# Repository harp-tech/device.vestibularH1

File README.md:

## Harp VestibularH1

This repository contains the device metadata, firmware and high-level interface to the VestibularH1 device. Below are simple getting started instructions for maintainers to create a new device using the automatic code generators.

### Device metadata

#### Prerequisites

1. Install [Visual Studio Code](https://code.visualstudio.com/)
2. Install the [YAML](https://marketplace.visualstudio.com/items?itemName=redhat.vscode-yaml) extension.

The `device.yml` file in the root of the project contains the VestibularH1 device metadata. A complete specification of device registers, including any bit masks, group masks, and payload specs needs to be provided for code generation to work.

### Generating interface and firmware

#### Prerequisites

1. Install [`dotnet`](https://dotnet.microsoft.com/)
2. Install `dotnet-t4`
```
dotnet tool install -g dotnet-t4
```

The `Generators` folder contains all text templates and project files required to generate both the firmware headers and the interface for the VestibularH1 device. To run the text templating engine just build the project inside this folder.

```
cd Generators
dotnet build
```

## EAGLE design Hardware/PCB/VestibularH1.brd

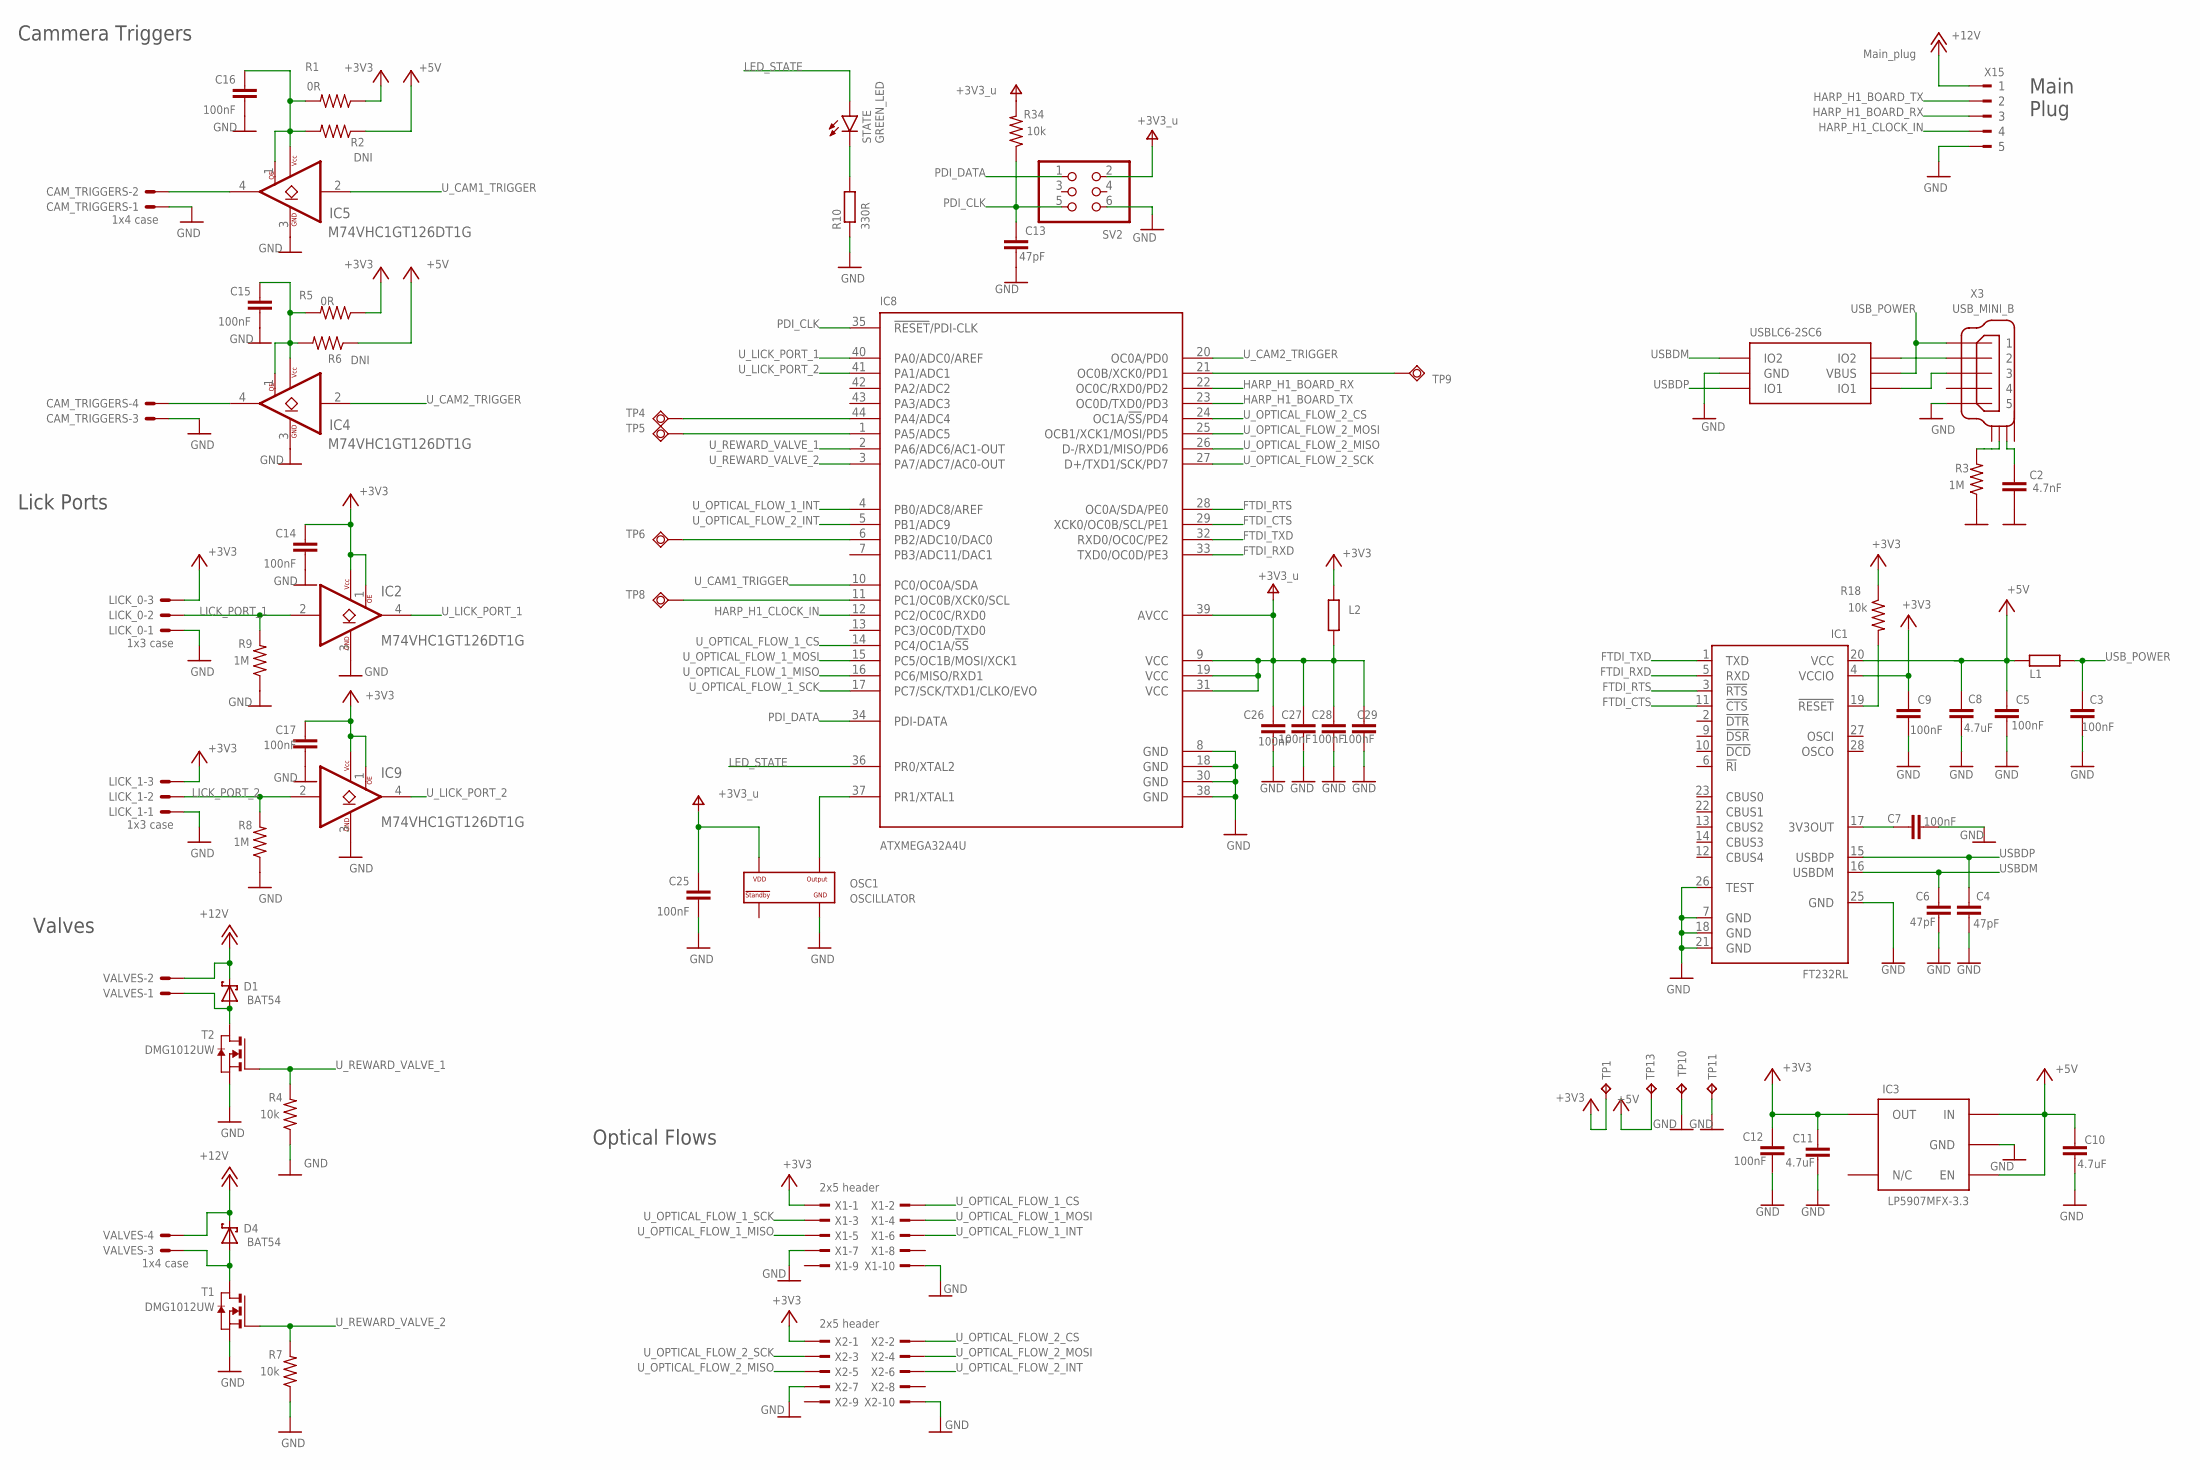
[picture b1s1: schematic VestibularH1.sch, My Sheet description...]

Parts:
C2: 4.7nF; C0402K; MPN CC0402KRX7R8BB472
C3, C5, C7, C9, C12, C14, C15, C16, C17, C25, C26, C27, C28, C29: 100nF; C0402K; MPN C1005X7R1H104K050BB; DIGIKEY_PN 445-5932-1-ND
C4, C6, C13: 47pF; C0402K; MPN 04025A470JAT2A
C8, C10: 4.7uF; C0603; MPN C1608X6S1C475K080AC
C11: 4.7uF; C0603K; MPN C1608X6S1C475K080AC
CAM_TRIGGERS: 1x4 case; 22-23-2041; MPN 282834-4
D1, D4: BAT54; SOT23; MPN BAT54SLT1G
IC1: FT232RL; SSOP28; MPN FT232RL
IC2, IC4, IC5, IC9: M74VHC1GT126DT1G; TSOP-5; MPN M74VHC1GT126DT1G; DIGIKEY_PN M74VHC1GT126DT1GOSDKR-ND
IC3: LP5907MFX-3.3; TSOT23-5; MPN LP5907MFX-3.3/NOPB
IC7: USBLC6-2SC6; SOT23-6L; MPN USBLC6-2SC6
IC8: ATXMEGA32A4U; TQFP44
L1, L2: 40R@100MHz; R0603; MPN MI0805K400R-10
LICK_0, LICK_1: 1x3 case; 22-23-2031; MPN 282834-3
OSC1: OSCILLATOR; OSCILLATOR_3.2X2.5; MPN DSC1001CI5-032.0000
R1, R5: 0R; R0402@1; MPN RC0402JR-070RL
R2, R6: DNI; R0402@1; MPN DNI
R3, R8, R9: 1M; R0402@1; MPN CRCW04021M00FKED; DIGIKEY_PN 541-1.00MLCT-ND
R4, R7, R18, R34: 10k; R0402@1; MPN CRCW040210K0FKED; DIGIKEY_PN 541-10.0KLDKR-ND
R10: 330R; R0402; MPN RC0402FR-07330RL
STATE: GREEN_LED; CHIP-LED0603; MPN LTST-C191KGKT
SV2: PINHD-2X3; 2X03; MPN 609-3210-ND
T1, T2: DMG1012UW; SOT323; MPN DMG1012UW-7
TP1, TP10, TP11, TP13: NO_COMPONENT; B1,27
TP4, TP5, TP6, TP8, TP9: NO_COMPONENT; TP11R
VALVES: 1x4 case; 22-23-2041; MPN 282834-4
X1, X2: 2x5 header; TSW-105-02-S-D; MPN 2x5 header
X3: USB_MINI_B; 240-0002-1; MPN UX60-MB-5S8
X15: Main_plug; 90G-5; MPN 20.155MH/5-E

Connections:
+3V3: C9.1, C11.1, C12.1, C14.1, C17.1, IC1.4 (VCCIO), IC2.1 (OE), IC2.5 (VCC), IC3.5 (OUT), IC9.1 (OE), IC9.5 (VCC), L2.2, LICK_0.3, LICK_1.3, R1.1, R5.1, R18.1, TP1.TP, X1.1, X2.1
+3V3_U: C25.1, C26.1, C27.1, C28.1, C29.1, IC8.9 (VCC), IC8.19 (VCC), IC8.31 (VCC), IC8.39 (AVCC), L2.1, OSC1.P$4 (VDD), R34.2, SV2.2
+5V: C5.1, C8.1, C10.1, IC1.20 (VCC), IC3.1 (IN), IC3.3 (EN), L1.1, R2.1, R6.1, TP13.TP
+12V: D1.3 (C), D4.3 (C), VALVES.2, VALVES.4, X15.1
FTDI_CTS: IC1.11 (!CTS), IC8.29 (XCK0/OC0B/SCL/PE1)
FTDI_RTS: IC1.3 (!RTS), IC8.28 (OC0A/SDA/PE0)
FTDI_RXD: IC1.5 (RXD), IC8.33 (TXD0/OC0D/PE3)
FTDI_TXD: IC1.1 (TXD), IC8.32 (RXD0/OC0C/PE2)
GND: C2.2, C3.2, C4.2, C5.2, C6.2, C7.2, C8.2, C9.2, C10.2, C11.2, C12.2, C13.2, C14.2, C15.2, C16.2, C17.2, C25.2, C26.2, C27.2, C28.2, C29.2, CAM_TRIGGERS.1, CAM_TRIGGERS.3, IC1.7 (GND), IC1.18 (GND), IC1.21 (GND), IC1.25 (GND), IC1.26 (TEST), IC2.3 (GND), IC3.2 (GND), IC4.3 (GND), IC5.3 (GND), IC7.P$2 (GND), IC8.8 (GND), IC8.18 (GND), IC8.30 (GND), IC8.38 (GND), IC9.3 (GND), LICK_0.1, LICK_1.1, OSC1.P$2 (GND), R3.1, R4.1, R7.1, R8.1, R9.1, R10.1, SV2.6, T1.2 (S), T2.2 (S), TP10.TP, TP11.TP, X1.7, X1.10, X2.7, X2.10, X3.P$5 (5), X15.5
HARP_H1_BOARD_RX: IC8.22 (OC0C/RXD0/PD2), X15.3
HARP_H1_BOARD_TX: IC8.23 (OC0D/TXD0/PD3), X15.2
HARP_H1_CLOCK_IN: IC8.12 (PC2/OC0C/RXD0), X15.4
LED_STATE: IC8.36 (PR0/XTAL2), STATE.A
LICK_PORT_1: IC2.2 (A), LICK_0.2, R9.2
LICK_PORT_2: IC9.2 (A), LICK_1.2, R8.2
unnamed: R3.2, X3.SHIELD_2
unnamed: IC7.P$4 (IO2), X3.P$2 (2)
unnamed: IC7.P$6 (IO1), X3.P$3 (3)
unnamed: CAM_TRIGGERS.4, IC4.4 (Y)
unnamed: C16.1, IC5.1 (OE), IC5.5 (VCC), R1.2, R2.2
unnamed: D4.1 (A), T1.3 (D), VALVES.3
unnamed: CAM_TRIGGERS.2, IC5.4 (Y)
unnamed: R10.2, STATE.C
unnamed: IC8.44 (PA4/ADC4), TP4.TP
unnamed: IC8.1 (PA5/ADC5), TP5.TP
unnamed: IC8.6 (PB2/ADC10/DAC0), TP6.TP
unnamed: C15.1, IC4.1 (OE), IC4.5 (VCC), R5.2, R6.2
unnamed: C2.1, X3.SHIELD_3
unnamed: IC8.11 (PC1/OC0B/XCK0/SCL), TP8.TP
unnamed: IC8.21 (OC0B/XCK0/PD1), TP9.TP
unnamed: C7.1, IC1.17 (3V3OUT)
unnamed: D1.1 (A), T2.3 (D), VALVES.1
unnamed: IC1.19 (!RESET), R18.2
OSC2: IC8.37 (PR1/XTAL1), OSC1.P$3 (OUTPUT)
PDI_CLK: C13.1, IC8.35 (!RESET!/PDI-CLK), R34.1, SV2.5
PDI_DATA: IC8.34 (PDI-DATA), SV2.1
USBDM: C6.1, IC1.16 (USBDM), IC7.P$3 (IO2)
USBDP: C4.1, IC1.15 (USBDP), IC7.P$1 (IO1)
USB_POWER: C3.1, IC7.P$5 (VBUS), L1.2, X3.P$1 (1)
U_CAM1_TRIGGER: IC5.2 (A), IC8.10 (PC0/OC0A/SDA)
U_CAM2_TRIGGER: IC4.2 (A), IC8.20 (OC0A/PD0)
U_LICK_PORT_1: IC2.4 (Y), IC8.40 (PA0/ADC0/AREF)
U_LICK_PORT_2: IC8.41 (PA1/ADC1), IC9.4 (Y)
U_OPTICAL_FLOW_1_CS: IC8.14 (PC4/OC1A/!SS), X1.2
U_OPTICAL_FLOW_1_INT: IC8.4 (PB0/ADC8/AREF), X1.6
U_OPTICAL_FLOW_1_MISO: IC8.16 (PC6/MISO/RXD1), X1.5
U_OPTICAL_FLOW_1_MOSI: IC8.15 (PC5/OC1B/MOSI/XCK1), X1.4
U_OPTICAL_FLOW_1_SCK: IC8.17 (PC7/SCK/TXD1/CLKO/EVO), X1.3
U_OPTICAL_FLOW_2_CS: IC8.24 (OC1A/!SS!/PD4), X2.2
U_OPTICAL_FLOW_2_INT: IC8.5 (PB1/ADC9), X2.6
U_OPTICAL_FLOW_2_MISO: IC8.26 (D-/RXD1/MISO/PD6), X2.5
U_OPTICAL_FLOW_2_MOSI: IC8.25 (OCB1/XCK1/MOSI/PD5), X2.4
U_OPTICAL_FLOW_2_SCK: IC8.27 (D+/TXD1/SCK/PD7), X2.3
U_REWARD_VALVE_1: IC8.2 (PA6/ADC6/AC1-OUT), R4.2, T2.1 (G)
U_REWARD_VALVE_2: IC8.3 (PA7/ADC7/AC0-OUT), R7.2, T1.1 (G)

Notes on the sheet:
Valves
Lick Ports
Cammera Triggers
Main Plug
Optical Flows

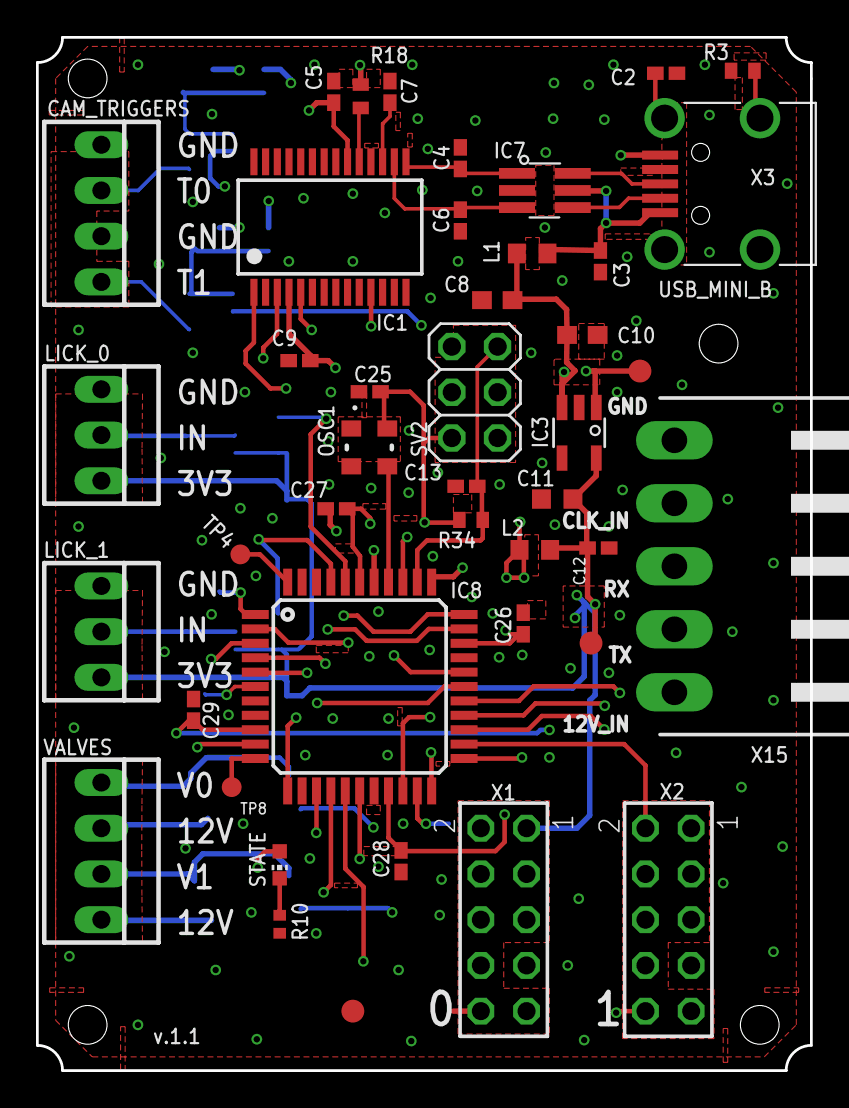
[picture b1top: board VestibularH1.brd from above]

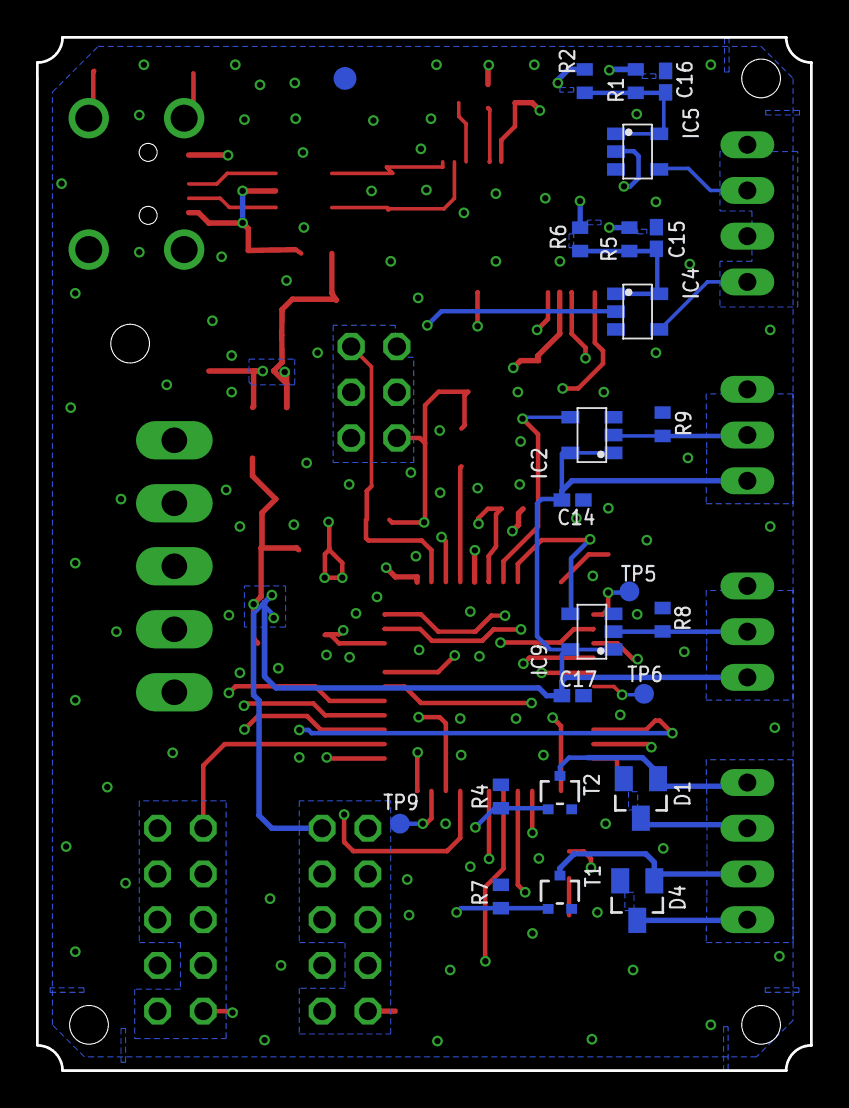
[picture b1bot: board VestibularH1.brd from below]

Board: 4 copper layers, 43.0 x 57.4 mm, 67 parts (24 on the bottom side), 55 nets.

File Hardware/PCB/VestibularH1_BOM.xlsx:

VestibularVR H1-module v.1.1 BOM
Qty | Parts | Value | OEPS | MPN | Device | Package | Description
2 | R1, R5 | 0R | OEPS020001 | RC0402JR-070RL | R-US_R0402 | R0402@1 | RESISTOR, American symbol
14 | C3, C5, C7, C9, C12, C14, C15, C16, C17, C25, C26, C27, C28, C29 | 100nF | OEPS010004 | C1005X7R1H104K050BB | C-EUC0402K | C0402K | CAPACITOR, European symbol
4 | R4, R7, R18, R34 | 10k | OEPS020030 | CRCW040210K0FKED | R-US_R0402 | R0402@1 | RESISTOR, American symbol
3 | R3, R8, R9 | 1M | OEPS020026 | CRCW04021M00FKED | R-US_R0402 | R0402@1 | RESISTOR, American symbol
2 | LICK_0, LICK_1 | 1x3 case | OEPS070035 | 282834-3 | 22-23-2031 | 22-23-2031 | .100 (2.54mm) Center Header - 3 Pin"
2 | CAM_TRIGGERS, REWARD_VALVES | 1x4 case | OEPS070036 | 282834-4 | 22-23-2041 | 22-23-2041 | .100 (2.54mm) Center Header - 4 Pin"
2 | X1, X2 | 2x5 header | n.a. | 2x5 header | TSW-105-02-S-D | TSW-105-02-S-D | THROUGH-HOLE .025 SQ POST HEADER"
1 | R10 | 330R | OEPS020037 | RC0402FR-07330RL | R-EU_R0402 | R0402 | RESISTOR, European symbol
1 | C2 | 4.7nF | OEPS010001 | CC0402KRX7R8BB472 | C-EUC0402K | C0402K | CAPACITOR, European symbol
3 | C8, C10, C11 | 4.7uF | OEPS010018 | C1608X6S1C475K080AC | C-EUC0603 | C0603 | CAPACITOR, European symbol
2 | L1, L2 | 40R@100MHz | OEPS040003 | MI0805K400R-10 | R-EU_R0603 | R0603 | RESISTOR, European symbol
3 | C4, C6, C13 | 47pF | n.a. | 04025A470JAT2A | C-EUC0402K | C0402K | CAPACITOR, European symbol
1 | IC8 | ATXMEGA32A4U | OEPS080012 | ATXMEGA32A4U-AUR | XMEGA-A4_AT-XMEGA-XXA4-AUTQFP44 | TQFP44 | ATxMega a4 Serie
2 | D1, D4 | BAT54 | OEPS030003 | BAT54SLT1G | BAT54 | SOT23 | Schottky Diodes
2 | T1, T2 | DMG1012UW | OEPS060010 | DMG1012UW-7 | DMG1012UW-7 | SOT323 | N-CHANNEL ENHANCEMENT MODE MOSFET
2 | R2, R6 | DNI | DNI | DNI | R-US_R0402 | R0402@1 | RESISTOR, American symbol
1 | IC1 | FT232RL | OEPS080013 | FT232RL | FT232RL | SSOP28 | UART/FIFO IC
1 | STATE | GREEN_LED | OEPS030005 | LTST-C191KGKT | LEDCHIP-LED0603 | CHIP-LED0603 | LED
1 | IC3 | LP5907MFX-3.3 | OEPS080016 | LP5907MFX-3.3/NOPB | TLV700XX | TSOT23-5 | C REG LINEAR 3.3V 200MA SOT23-5
4 | IC2, IC4, IC5, IC9 | M74VHC1GT126DT1G | OEPS080017 | M74VHC1GT126DT1G | M74VHC1GT126DT1G | TSOP-5 | Single Buffer/Driver With Open-Drain Output
1 | X15 | Main_plug | OEPS070037 | 20.155MH/5-E | 90G-5 | 90G-5 | WEIDMUELLER CLAMP CONNECTOR
1 | OSC1 | OSCILLATOR | OEPS080018 | DSC1001CI5-032.0000 | OSCILLATOR | OSCILLATOR_3.2X2.5 | XTAL OSC TCXO 32.0000MHZ HCMOS
1 | SV2 | PINHD-2X3 | OEPS070015 | 609-3210-ND | PINHD-2X3 | 2X03 | PIN HEADER
1 | X3 | USB_MINI_B | OEPS070021 | UX60-MB-5S8 | USB_MINI_B | 240-0002-1 | CONN RCPT USB2.0 MINI B SMD R/A
1 | IC7 | USBLC6-2SC6 | OEPS030010 | USBLC6-2SC6 | USBLC6-2SC6 | SOT23-6L | TVS DIODE 5.25VWM 17VC SOT23-6
.off board
Qty | Value | Parts | OEPS | Device | MPN | Package | Description
1 | CONN RCPT 10POS IDC 28AWG | n.a. | OEPS070040 | - | 1658621-1 AKC10H-ND | 2x5 10mil pitch | IDC 2x5 10mil pitch
1 | PAA5100JE Near Optical Flow Camera SPI Breakout | n.a. | OEPS ?? | - | PAA5100JE | - | PAA5100JE-Q is PixArt Imaging's latest optical navigation chip
2 | Lick Sensor module v1.0 PCB | n.a. | OEPS ?? | - | Lick Sensor module v1.0 | - | Lick Sensor
1 | Pluggable Terminal Block, 3.5 mm, 5 Ways | n.a. | OEPS070038 | - | 20.1550M/5-E Farnell 2575218 | - | External Terminal Block
n | flat ribbon cable | n.a. | OEPS090003 | - | 3365/10-100SF | - | RIBON 10COND 28AWG GRAY 100FT 30.48metter

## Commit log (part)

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2022-09-19 \_docsss & datasheets reorganized
2022-10-06 VestibularVR H1-module v1.0: PCB design update
    VestibularVR H1-module v1.0 design
    - Eagle migration
    - start buffering & PCB integration & size
    - plugs & headers not selected yet; but on schm already
2022-10-09 pcb v1.0 developed
2022-10-13 proceeding design VestibularVR H1
    - Eagle version changed back to v.8.3.1
    - proceeding design VestibularVR H1-module v1.0
    - added Lick Sensor module v1.0
2022-10-14 update on VestibularVR & LickSensor
    - returned to Eagle 9.6.2
    - projects reviewed with Filipe
    - LickSensor board with reviews already made
    - VestibularVR board starting implementing reviews
2022-10-31 VestibularVR H1-module v1.0 - revisions made with Filipe updated
    Revisions made:
    - added missing decoupler caps
    - considered components on top & bottom side
    - review pinout on micro
    Next steps:
    - final mechanical integration
2022-11-03 . schm design reviewed 2nd time with Filipe . pcb design already started; not finished
2022-11-04 same as last commit: . procceding pcb design
2022-11-04 . pcb design; not finnished
2022-11-07 . 1st stage pcb design finnalized . missing: . put couple test poitns . move mechanical hole from one to other side usb plug . Filipe going to do a revision
2022-11-07 v.1.0 pcb design as finished; still missing to hear about it from Filipe
    . David's pcb v.1.0 design as finished
    - mechanical holes final tuning
    - main labels final design
    . still missing to hear about it from Filipe
    . next step - building BOM
2022-11-09 final versions committed & CAM data
    VestibularVR H1-module v1.0
    &
    Lick Sensor module v1.0
    final versions committed !!!
    .created CAM data for both boards
2022-11-09 tunings on last versions
    tunings on last versions:
    - labels size & positions
    - VestibularVR H1 module get 1mm more height
2022-11-14 BOMs building
    . BOMs building:
    - for both projects - Lick Sensor Module v1.0 & VestibularVR H1 Module v1.0
    - schm files modified (components parameters updated)
    . Removed old Auxiliary Designs
2022-11-21 BOM files
    BOM files
    - Lick sensor module v1.0 BOM; NOT FINAL
    VESTIBULARVR H1 v.1.0: added schm notes
    - VESTIBULARVR H1 v.1.0 BOM; NOT FINAL
2022-11-21 BOM being updated
    BOM being updated
    not yet finished
2022-11-22 BOMs & start Harp Motor device H2-module v1.0
    . almost final BOMs versions for VestibularVR H1-module v1.0 & Lick Sensor module v1.0
    . start of new project Harp Motor device H2-module v1.0
2022-11-25 VestibularVR H1 module & Lick Sensor module v1.0 FINAL BOMs
    final BOM versions
    . VestibularVR H1 module
    . Lick Sensor module v1.0
2022-12-05 VestibularVR H1BOM updates & Lick Sensor step on
    - VestibularVR H1
    . component ref updated
    . BOM file updated
    - Lick Sensor module v1.0
    . still only on schematic design
2023-01-06 >> VestibularVR H1-module v1.0: corrected part numbers
    >> VestibularVR H1-module v1.0
    - notes added on schematic
    . buffers with wrong pn - corrected OEPS code; still wrong buffers' symbol
    generated new BOM with corrected pn
2023-01-15 Reorganize repository to match standard template
2023-01-15 Raised firmware version to 1.0.
2023-01-15 Initial commit of firmware files.
    Already implements the valves, the cameras, and the lick inputs.
2023-01-15 Minor corrections on descriptions.
2023-01-15 Added optical flow reading on both ports.
2023-01-15 Added control of both cameras.
2023-01-15 Added a bonsai workflow useful for tests and debug.
    Added a bonsai workflow that helps with tests and debug.
2023-01-16 Refactor firmware references to match device name
2023-02-13 Update editorconfig and gitignore files
2023-02-13 Add first iteration of auto generated interface
2023-02-13 Fix device interface specification
2023-04-21 Add license file
2023-04-21 Update source generators and device metadata
2023-09-01 Replaced harp core 1.12 with 1.13.
2023-09-05 Replaced files with version 1.1.
2023-09-05 Replaced BOM with version 1.1.
2023-10-14 Corrected product ID verification.
2023-10-14 Increased delay after reset for power up time.
2023-10-14 Added SPI mode 3 and initial flow meter verification.
2023-10-14 Added first PMW3360 code.
2023-10-14 Added ability to recognize the PMW3360.
2023-10-14 Fixed used flow meter selection.
2023-10-14 Major update.
    Includes the entire code for the flow meter PMW3360.
2023-10-14 Created he new registers.
    Registers list:
    ADD_REG_PRODUCT_ID_PORT0 47 U8
    ADD_REG_PRODUCT_ID_PORT1 48 U8
    ADD_REG_CPI 49 U16
2023-10-14 Created functionality to read the flow meter ID.
2023-10-14 Implemented functionality to change the counts per inch.
2023-10-14 Timing corrected.
2023-10-14 Added limit to register CPI.
2023-11-27 Update generator package and regenerate interface
2023-11-27 Move interface license file
2024-06-27 Added the new registers.
2024-06-27 Added description payload specification.
2024-06-27 Implemented algorithm and added boundaries.
2024-06-28 Implemented serial TX.
2024-06-28 Fixed bad serial initialization.
2024-06-28 Raised firmware version.
